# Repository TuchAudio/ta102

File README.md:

# TuchAudio 102
Discrete, _tube-like_ phono preamp.

_**NO LONGER RECOMMENDED, use [TuchAudio 103](../../../ta103) instead.**_

## Purpose
Discrete, non-op-amp classic design phono preamp, made as simple as possible.

## Design quirks
_After_ the original PCB was ordered, overload margin was deemed insufficient; thus a **hack** was made, essentialy _swapping the two first stages_ of the preamp.

DIN and RCA jacks are provided for signal input. Since the _native_ input impedance is around **110 kΩ**, space for suitable load (`Rx` and `Cx`) is provided for perfect adaptation; but for added flexibility, it is possible to use the free input for a suitable RC combo in parallel, to match the appropriate cartridge load.

Originally intended to be connected thru the [501 Input Selector board](../../../ta501), both output pins and power input are at compatible locations within each board. An aditional RCA **output** jack can be installed in order to use the circuit as a _stand-alone preamp_.

### Stability

As any other amplifier with _asymmetrical power supply_, the PSRR is very poor, thus a **well filtered, stable** power supply is essential. Increasing (within reason) `R114/R214` may help a bit.

This circuit has proved to be _quite sensitive to capacitor quality_, especially at `C102/C103/C202/C203` positions which, in some cases, may lead to **instability**. For all these reasons we recommend using the [103 Phono Preamp](../../../ta103) instead, which is a direct replacement in the very **same form factor**.

### Suggested mods

#### Standalone mode

Despite being designed around a 12 Volt power supply, this can be run from a single **9 Volt battery**, with minor changes and similar performance.

- `R114/R214`: use **120 Ω** instead of 180.
- `R111/R211`: use **2.7 kΩ** instead of 3K3.
-  ...

#### IEC1976/Neumann ammendments

The stated values are designed around these _ammendments_ to the **RIAA curve**; but since they're currently _deprecated_, you may get **improved bass response** by turning back to RIAA correction:

- `C105/C205`: do not mount (Neumann ammendment)
- `C107/C207`: use **220 nF** or more instead of 100 nF (which made a _-3 dB point at 20 Hz_ **over 108 kΩ** of the _501 board_ input)

## Specs

- **Power supply:** 9-12 V, asymmetrical, max. 6 mA
- **Input connectors:** 2x RCA plus DIN (in parallel)
- **Gain at 1 kHz:** 50x (+34 dB)
- **Input sensitivity:** 3.6 mV (for 180 mV output)
- **Input impedance:** 108 kΩ; adjusted by `Rx/Cx`, either internal or external.
- **Output level and impedance:** 180 mV / 3.3 KΩ
- **Overload margin:** at least +15 dB
- **Signal-to-noise ratio:** TBD
- **Frequency response:** 32 Hz - 20 kHz _(+1.5/-2 dB deviation from RIAA; -3 dB beyond audible range)_
- **Distortion:** (most notably from **2nd harmonic**, which may resemble **tube sound**)

| Harmonic | nominal output | +15 dB overload |
| -------- | -------------- | --------------- |
| 2nd      | 0.55 %         | **8 %**         |
| 3rd      | 0.16 %         | 0.59 %          |
| 4th      | 0.08 %         | 0.28 %          |
| 5th      | negligible     | 0.08 %          |

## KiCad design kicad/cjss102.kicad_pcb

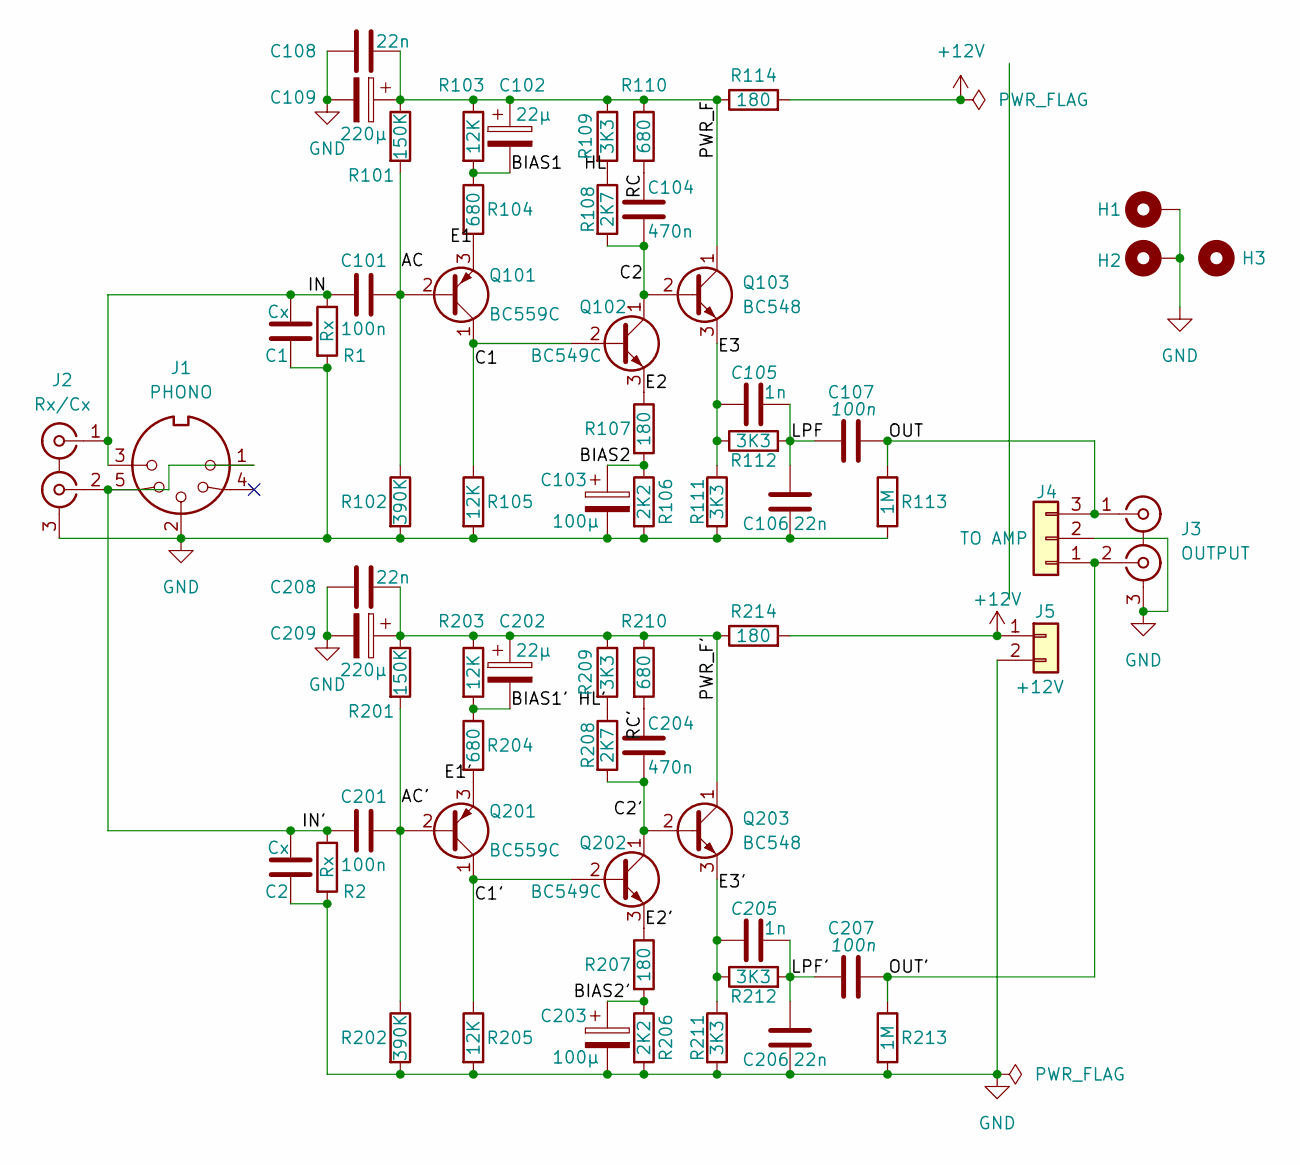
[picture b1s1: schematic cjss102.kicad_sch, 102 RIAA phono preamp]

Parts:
C1, C2: Cx; PinSocket_1x02_P2.54mm_Vertical
C101, C107, C201, C207: 100n; C_Rect_L7.2mm_W2.5mm_P5.00mm_FKS2_FKP2_MKS2_MKP2
C102, C202: 22µ; CP_Radial_D4.0mm_P1.50mm
C103, C203: 100µ; CP_Radial_D4.0mm_P1.50mm
C104, C204: 470n; C_Rect_L7.2mm_W3.0mm_P5.00mm_FKS2_FKP2_MKS2_MKP2
C105, C205: 1n; C_Rect_L7.2mm_W2.5mm_P5.00mm_FKS2_FKP2_MKS2_MKP2
C106, C206: 22n; C_Rect_L7.2mm_W2.5mm_P5.00mm_FKS2_FKP2_MKS2_MKP2
C108, C208: 22n; C_Disc_D6.0mm_W2.5mm_P5.00mm
C109, C209: 220µ; CP_Radial_D6.3mm_P2.50mm
H1, H2: MountingHole_Pad; MountingHole_3.2mm_M3_DIN965_Pad
H3: MountingHole; MountingHole_3.2mm_M3
J1: PHONO; DIN 5-180deg
J2: Rx/Cx; 2xRCA_vertical
J3: OUTPUT; 2xRCA_vertical
J4: TO AMP; PinHeader_1x03_P2.54mm_Horizontal
J5: +12V; PinHeader_1x02_P2.54mm_Horizontal
Q101, Q201: BC559C; TO-92_Inline
Q102, Q202: BC549C; TO-92_Inline
Q103, Q203: BC548; TO-92_Inline
R1, R2: Rx; PinSocket_1x02_P2.54mm_Vertical
R101, R201: 150K; R_Axial_DIN0207_L6.3mm_D2.5mm_P10.16mm_Horizontal
R102, R202: 390K; R_Axial_DIN0207_L6.3mm_D2.5mm_P10.16mm_Horizontal
R103, R105, R203, R205: 12K; R_Axial_DIN0207_L6.3mm_D2.5mm_P10.16mm_Horizontal
R104, R110, R204, R210: 680; R_Axial_DIN0207_L6.3mm_D2.5mm_P10.16mm_Horizontal
R106, R206: 2K2; R_Axial_DIN0207_L6.3mm_D2.5mm_P10.16mm_Horizontal
R107, R114, R207, R214: 180; R_Axial_DIN0207_L6.3mm_D2.5mm_P10.16mm_Horizontal
R108, R208: 2K7; R_Axial_DIN0207_L6.3mm_D2.5mm_P10.16mm_Horizontal
R109, R111, R112, R209, R211, R212: 3K3; R_Axial_DIN0207_L6.3mm_D2.5mm_P10.16mm_Horizontal
R113, R213: 1M; R_Axial_DIN0207_L6.3mm_D2.5mm_P10.16mm_Horizontal

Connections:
+12V: J5.1, R114.2, R214.2
/AC: C101.2, Q101.2 (B), R101.2, R102.1
/AC': C201.2, Q201.2 (B), R201.2, R202.1
/BIAS1: C102.2, R103.2, R104.1
/BIAS1': C202.2, R203.2, R204.1
/BIAS2: C103.1, R106.1, R107.2
/BIAS2': C203.1, R206.1, R207.2
/C1: Q101.1 (C), Q102.2 (B), R105.1
/C1': Q201.1 (C), Q202.2 (B), R205.1
/C2: C104.2, Q102.1 (C), Q103.2 (B), R108.2
/C2': C204.2, Q202.1 (C), Q203.2 (B), R208.2
/E1: Q101.3 (E), R104.2
/E1': Q201.3 (E), R204.2
/E2: Q102.3 (E), R107.1
/E2': Q202.3 (E), R207.1
/E3: C105.1, Q103.3 (E), R111.1, R112.1
/E3': C205.1, Q203.3 (E), R211.1, R212.1
/HL: R108.1, R109.2
/HL': R208.1, R209.2
/IN: C1.1, C101.1, J1.3, J2.1 (IN1), R1.1
/IN': C2.1, C201.1, J1.1, J1.5, J2.2 (IN2), R2.1
/LPF: C105.2, C106.1, C107.1, R112.2
/LPF': C205.2, C206.1, C207.1, R212.2
/OUT: C107.2, J3.1 (IN1), J4.3, R113.1
/OUT': C207.2, J3.2 (IN2), J4.1, R213.1
/PWR_F: C102.1, C108.2, C109.1, Q103.1 (C), R101.1, R103.1, R109.1, R110.1, R114.1
/PWR_F': C202.1, C208.2, C209.1, Q203.1 (C), R201.1, R203.1, R209.1, R210.1, R214.1
/RC: C104.1, R110.2
/RC': C204.1, R210.2
GND: C1.2, C2.2, C103.2, C106.2, C108.1, C109.2, C203.2, C206.2, C208.1, C209.2, H1.1, H2.1, J1.2, J2.3 (EXT), J3.3 (EXT), J4.2, J5.2, R1.2, R2.2, R102.2, R105.2, R106.2, R111.2, R113.2, R202.2, R205.2, R206.2, R211.2, R213.2

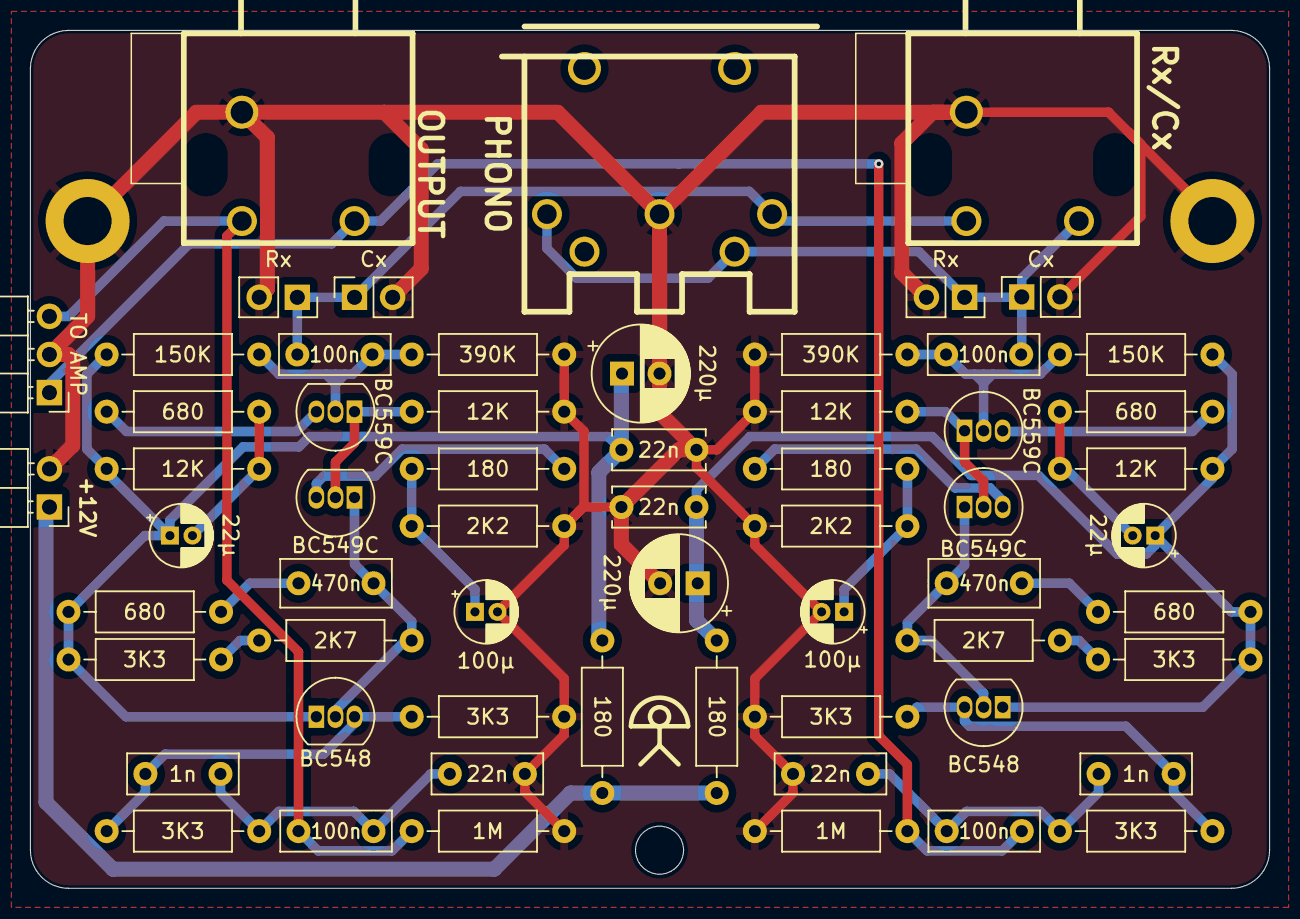
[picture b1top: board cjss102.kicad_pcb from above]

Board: 2 copper layers, 82.5 x 57.1 mm, 64 parts (0 on the bottom side), 30 nets.

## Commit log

2025-11-08 add KiCAD files
2025-11-24 attempt to fix links
2025-11-24 second attempt
